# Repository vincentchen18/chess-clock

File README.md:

# Chess Clock

## Overview

If anyone has been looking at my [Github Profile](https://github.com/vincentchen18), they may be quite aware of my active participation in the sport of chess. Hence, this project would seem fairly derivative. 

This project is an addition to my already existing chess projects, which includes:

- [My chess engine project](https://github.com/vincentchen18/chess-engine), a roughly 1700 rated chess bot made from pygame

- [My 3D chess set model](https://github.com/vincentchen18/board-game-set), a printable chessboard with which this clock is designed to go with.

This project includes a printed circuit board, as well as a 3D modelled chess clock shell designed to fit the PCB, complete with button caps.

The clock is also noticeably quite small. (pcb size < 100mm x 100mm). Yes, the player buttons are quite sketchy and diagonal. This is because they are angled with the PCB

This project is also built for week 4, displays, of Hack Club's [Half Life YSWS](halflife.hackclub.com) program.

## Schematics

Above is the schematics for this chess clock project, made in KiCad. The project includes a XIAO-ESP32-C3, 2 four 7segment digit displays, as well as a bunch of switches/buttons and resistors.

The Printed Circuit Board layout is below.

## Hardware & Assembly

This is the PCB render of my project.

The keys/switches need to be stuck onto the switch parts.

Then, the case for the chess clock must be printed.

Then, to assemble the final Chess Clock, you first need to complete assembly of the PCB, then, attach the buttons and the keycaps from the 3D print file, located [here](3D%20Models/Printing%20Assembly.stl), which needs to be printed.

After attaching the keycaps, place the PCB inside the top print, ensuring that the buttons go in the correct holes and that displays poke through and can be seen. Also ensure that you can access the switch and the USB plug from the back of the case, as the clock requires that hole for charging.

Finally, place the bottom piece into the top piece, (there is around 0.2mm of tolerance), and it should friction fit on, holding the pcb in place.

That's it!! just push the firmware code into the pcb and it's done.

## Features and Controls

** Please note that the clock is not configured to be able to set uneven time intervals (so no time odds :C). It is not recommended that you challenge a master using this clock (if you're an unskilled player like me of course)**

This clock features: 

- 10 time control presets, as well as custom adjustable time controls using the 4 buttons.

- Fischer, Bronstein, and Delay increment modes

- Turn indicator: a dot lights up the player whose time is currently running.

- Time Scramble Mode and Low Time Warning: switches to display seconds and partial seconds when you are low on time, and beeps the buzzer to tell you that you're low on time when your clock reaches <10s.

- Move counter, which is shown while the clock is paused. (most clocks don't have this :DDD)

- Buzzer beeps for each move and also when someone flags, as well as low time warning, which is optionally mutable.

- LiPo Power with USB-C Charging through the XIAOESP32C3

- Battery Voltage on boot, low battery warning, and autoshutdown if battery is too low (remember to charge your clock! :33)

- Autosleep when idle for too long

- Settings saved across power off.

### Setup Menu

The setup menu in my clock is a bit unconventional compared to other clocks. Since both players' times are always equal, the left display shows the time in minutes, while the display on the right shows the increment type and the increment amount.

Other controls:

| Button | State | Action |
|---|---|---|
| Left / Right | Ready | Start the **other** player's clock |
| Left / Right | Your turn | End your turn, start your opponent's |
| Left / Right | Asleep | Wake the clock |
| Pause (tap) | Running | Pause — displays alternate time / move count |
| Pause (tap) | Paused | Resume |
| Pause (hold 1 s) | Any (except setup) | Reset both clocks |
| Mode (tap) | Ready / Flagged | Enter setup |
| − (hold 1 s) | Ready | Toggle sound on / off |
| Mode (tap) | Setup | Next field: preset → base time → increment → type |
| + / − | Setup | Change the blinking value |
| Pause (tap) | Setup | Save and exit |

From left to right, the buttons are +, -, mode, and pause.

That's it! :DD

## AI Usage

AI was not used during the entirety of the creation of this project.

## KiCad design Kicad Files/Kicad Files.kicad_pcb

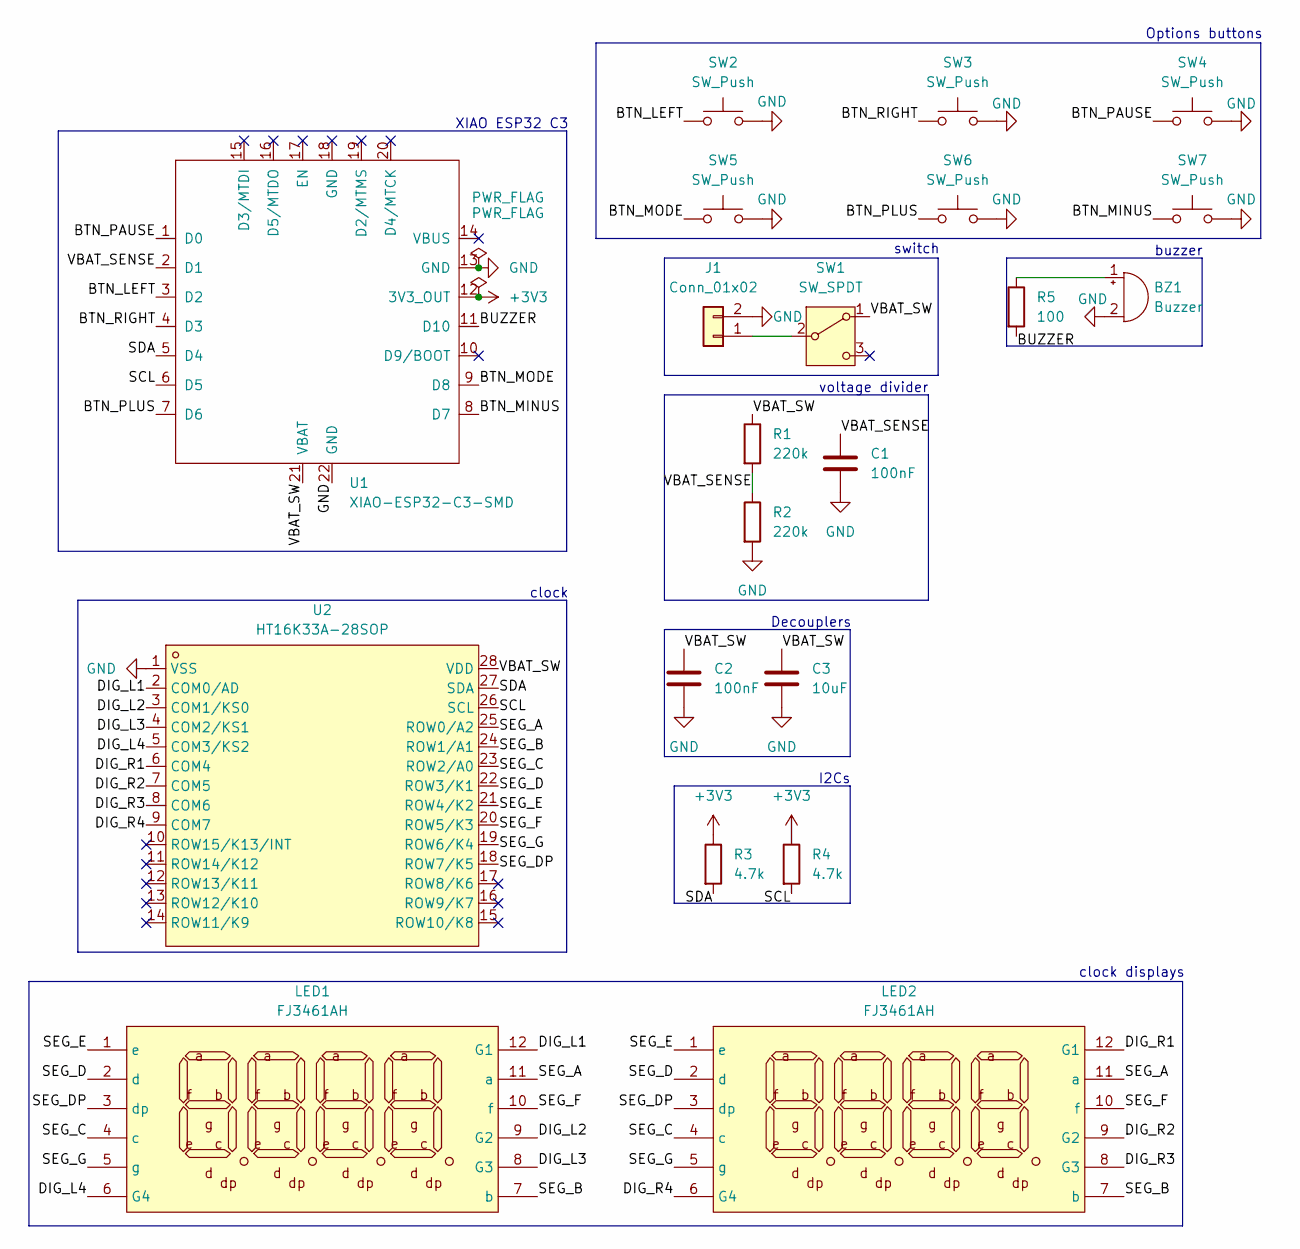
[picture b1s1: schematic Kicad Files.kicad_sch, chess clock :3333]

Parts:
BZ1: Buzzer; BUZ-TH_BD12.0-P6.50-D0.8-FD
C1, C2: 100nF; C_0805_2012Metric
C3: 10uF; C_0805_2012Metric
J1: Conn_01x02; JST_PH_S2B-PH-SM4-TB_1x02-1MP_P2.00mm_Horizontal
LED1, LED2: FJ3461AH; LED-SEG-TH_12P-L30.0-W14.0-P2.54-S10.16-BL; MPN FJ3461AH; LCSC Part C10708
R1, R2: 220k; R_Axial_DIN0207_L6.3mm_D2.5mm_P7.62mm_Horizontal
R3, R4: 4.7k; R_Axial_DIN0207_L6.3mm_D2.5mm_P7.62mm_Horizontal
R5: 100; R_Axial_DIN0207_L6.3mm_D2.5mm_P7.62mm_Horizontal
SW1: SW_SPDT; SW_SPDT_PCM12
SW2, SW3: SW_Push; SW_PUSH-12mm
SW4, SW5, SW6, SW7: SW_Push; SW_PUSH_6mm
U1: XIAO-ESP32-C3-SMD
U2: HT16K33A-28SOP; SOP-28_L17.9-W7.5-P1.27-LS10.3-BL; MPN HT16K33A-28SOP; LCSC Part C5444737

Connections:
+3V3: R3.1, R4.1, U1.12 (3V3_OUT)
/BTN_LEFT: SW2.1, U1.3 (D2)
/BTN_MINUS: SW7.1, U1.8 (D7)
/BTN_MODE: SW5.1, U1.9 (D8)
/BTN_PAUSE: SW4.1, U1.1 (D0)
/BTN_PLUS: SW6.1, U1.7 (D6)
/BTN_RIGHT: SW3.1, U1.4 (D3)
/BUZZER: R5.2, U1.11 (D10)
/DIG_L1: LED1.12 (G1), U2.2 (COM0/AD)
/DIG_L2: LED1.9 (G2), U2.3 (COM1/KS0)
/DIG_L3: LED1.8 (G3), U2.4 (COM2/KS1)
/DIG_L4: LED1.6 (G4), U2.5 (COM3/KS2)
/DIG_R1: LED2.12 (G1), U2.6 (COM4)
/DIG_R2: LED2.9 (G2), U2.7 (COM5)
/DIG_R3: LED2.8 (G3), U2.8 (COM6)
/DIG_R4: LED2.6 (G4), U2.9 (COM7)
/SCL: R4.2, U1.6 (D5), U2.26 (SCL)
/SDA: R3.2, U1.5 (D4), U2.27 (SDA)
/SEG_A: LED1.11 (a), LED2.11 (a), U2.25 (ROW0/A2)
/SEG_B: LED1.7 (b), LED2.7 (b), U2.24 (ROW1/A1)
/SEG_C: LED1.4 (c), LED2.4 (c), U2.23 (ROW2/A0)
/SEG_D: LED1.2 (d), LED2.2 (d), U2.22 (ROW3/K1)
/SEG_DP: LED1.3 (dp), LED2.3 (dp), U2.18 (ROW7/K5)
/SEG_E: LED1.1 (e), LED2.1 (e), U2.21 (ROW4/K2)
/SEG_F: LED1.10 (f), LED2.10 (f), U2.20 (ROW5/K3)
/SEG_G: LED1.5 (g), LED2.5 (g), U2.19 (ROW6/K4)
/VBAT_SENSE: C1.1, R1.2, R2.1, U1.2 (D1)
/VBAT_SW: C2.1, C3.1, R1.1, SW1.1 (A), U1.21 (VBAT), U2.28 (VDD)
GND: BZ1.2 (-), C1.2, C2.2, C3.2, J1.2, R2.2, SW2.2, SW3.2, SW4.2, SW5.2, SW6.2, SW7.2, U1.13 (GND), U1.22 (GND), U2.1 (VSS)
unnamed: BZ1.1 (+), R5.1
unnamed: J1.1, SW1.2 (B)

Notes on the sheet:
voltage divider
switch
Options buttons
Decouplers
clock
clock displays
I2Cs
buzzer
XIAO ESP32 C3

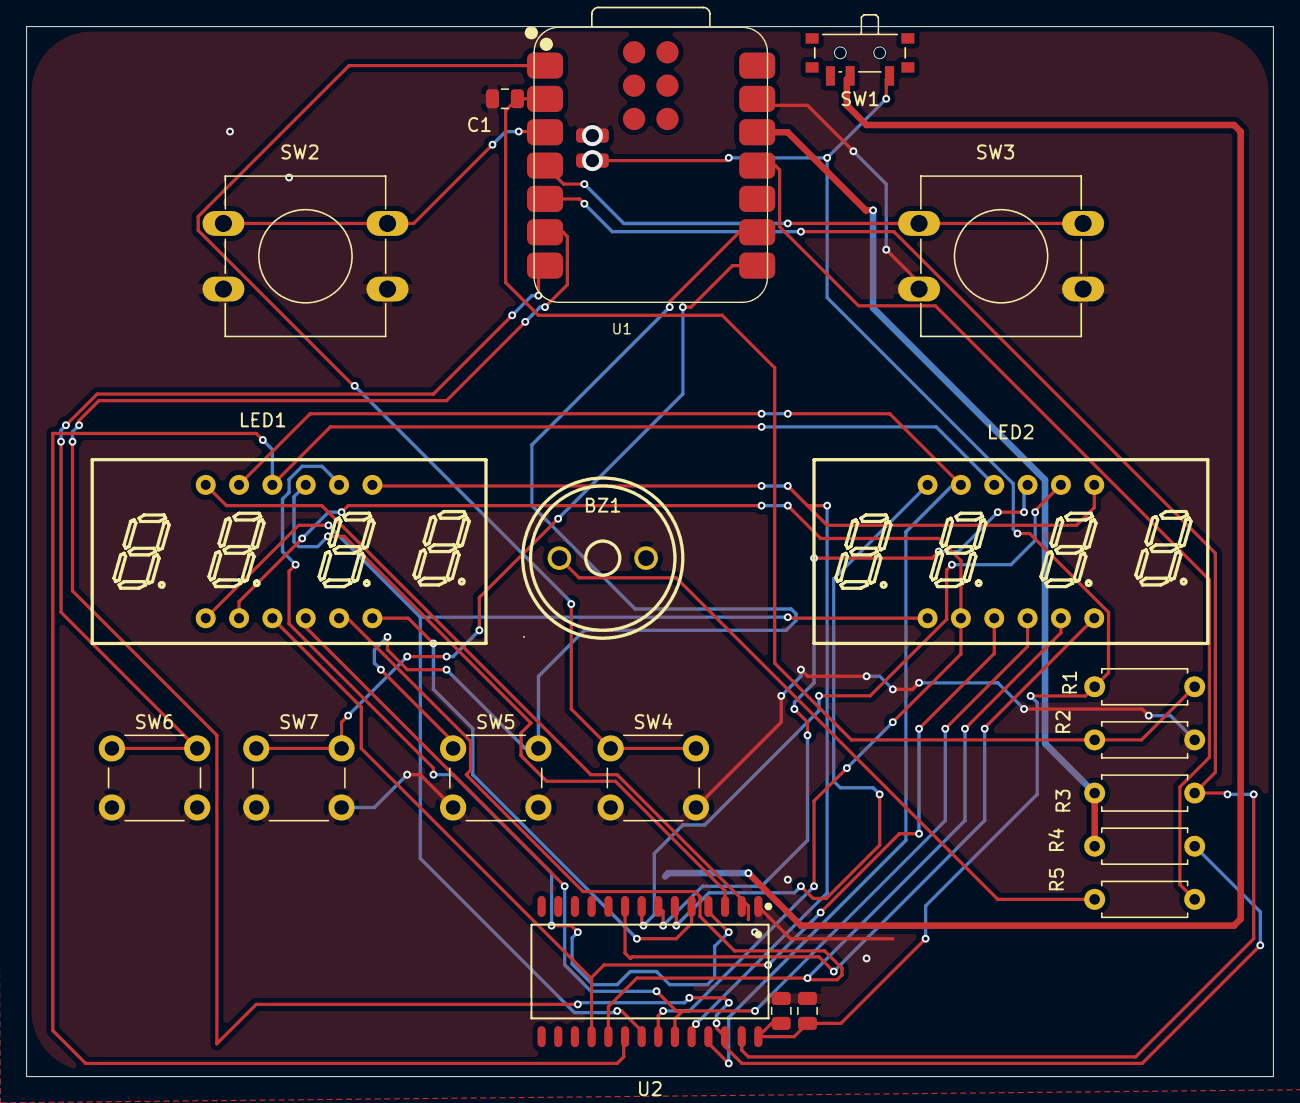
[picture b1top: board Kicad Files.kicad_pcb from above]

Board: 2 copper layers, 95.0 x 80.0 mm, 21 parts (1 on the bottom side), 31 nets.

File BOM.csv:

Ref,Part,Qty to order,Qty used,Unit price (USD),Total (USD),Supplier,Part #,Link
U2,HT16K33A-28SOP LED driver,1,1,0.75,0.75,LCSC,C5444737,https://www.lcsc.com/product-detail/C5444737.html
"LED1, LED2",FJ3461AH 0.36in 4-digit 7-seg common cathode,2,2,0.67,1.34,LCSC,C10708,https://www.lcsc.com/product-detail/C10708.html
"C1, C2",100nF 0805 capacitor,20,2,0.02,0.41,LCSC,C49678,https://www.lcsc.com/product-detail/C49678.html
C3,10uF 0805 capacitor,20,1,0.04,0.88,LCSC,C15850,https://www.lcsc.com/product-detail/C15850.html
SW1,PCM12SMTR slide switch,1,1,1.28,1.28,LCSC,C221841,https://www.lcsc.com/product-detail/C221841.html
J1,JST S2B-PH-SM4-TB battery connector,5,1,0.23,1.14,LCSC,C295747,https://www.lcsc.com/product-detail/C295747.html
BZ1,GPC12075YB-5V passive piezo buzzer,1,1,0.56,0.56,LCSC,C252948,https://www.lcsc.com/product-detail/C252948.html
SW4-SW7,6x6x11mm tactile switch THT,10,4,0.04,0.39,LCSC,C720305,https://www.lcsc.com/product-detail/C720305.html
"SW2, SW3",12x12x7.3mm tactile switch THT,10,2,0.07,0.66,LCSC,C231717,https://www.lcsc.com/product-detail/C231717.html
U1,Seeed XIAO ESP32-C3,1,1,0.97,0.97,AliExpress,Welcome Deal (AUD 1.49),
BT1,LiPo 503450 3.7V 1000mAh JST PH2.0,1,1,6.45,6.45,AliExpress,AUD 9.89,https://www.aliexpress.com/item/1005012823920013.html
PCB,Chess clock PCB 80x95mm 2-layer,5,1,0.80,4.00,JLCPCB,,https://jlcpcb.com
"R1, R2",220k resistor 1/4W THT,2,2,0.00,0.00,Owned (resistor kit),,
"R3, R4",4.7k resistor 1/4W THT,2,2,0.00,0.00,Owned (resistor kit),,
R5,100 ohm resistor 1/4W THT,1,1,0.00,0.00,Owned (resistor kit),,
,TOTAL (before shipping),,,,18.83,,,

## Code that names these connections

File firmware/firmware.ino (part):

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#include "driver/gpio.h"

//pins
#define PIN_BTN_PAUSE D0
#define PIN_VBAT      D1
#define PIN_BTN_LEFT  D2
#define PIN_BTN_RIGHT D3
#define PIN_SDA       D4
#define PIN_SCL       D5
#define PIN_BTN_PLUS  D6
#define PIN_BTN_MINUS D7
#define PIN_BTN_MODE  D8
#define PIN_BUZZER    D10

#define HT_ADDR 0x70
struct Button {
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

//digit segment bits
#define SEG_DP 0x80
const uint8_t DIGITS[10] {
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};
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bool soundOn = true;

void beep(uint16_t freq, uint16_t ms) {
  if (soundOn) tone(PIN_BUZZER, freq, ms);
}

//messages
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


Button btnLeft = {PIN_BTN_LEFT};
Button btnRight = {PIN_BTN_RIGHT};
Button btnPause = {PIN_BTN_PAUSE};
Button btnMode = {PIN_BTN_MODE};
Button btnPlus = {PIN_BTN_PLUS};
Button btnMinus = {PIN_BTN_MINUS};

void btnInit(Button& b) {
  pinMode(b.pin, INPUT_PULLUP);
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  htFlush();
  htCmd(0x80);
  htCmd(0x20);
  gpio_pullup_en((gpio_num_t)PIN_BTN_LEFT);
  gpio_pullup_en((gpio_num_t)PIN_BTN_RIGHT);
  uint64_t mask = (1ULL << PIN_BTN_LEFT) | (1ULL << PIN_BTN_RIGHT); // wake up if either player button is clicked
  esp_deep_sleep_enable_gpio_wakeup(mask, ESP_GPIO_WAKEUP_GPIO_LOW);
  esp_deep_sleep_start();
}
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  btnInit(btnMode);
  btnInit(btnPlus);
  btnInit(btnMinus);
  pinMode(PIN_BUZZER, OUTPUT);
  prefs.begin("clock", false);
  loadSettings();
  setText(0, "HI  ");
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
